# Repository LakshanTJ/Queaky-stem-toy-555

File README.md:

# 🎵 Queaky STEM Toy using 555 Timer 

A beginner-friendly **embedded systems project** that generates a squeaky sound using the **555 Timer IC in astable mode**.
This project demonstrates the complete workflow from **circuit design →  PCB design using KiCad**.

---

## 🧰 Components Used

* IC 555 Timer ×1
* 9V Battery ×1
* 9V Battery Connector ×1
* 5–12V Buzzer ×1
* 1kΩ Resistor ×1
* 10kΩ Resistor ×1
* 1nF Ceramic Capacitor ×1
* 100µF Electrolytic Capacitor ×1
* Breadboard / PCB

---

## ⚙️ How It Works

The circuit uses the **555 Timer in astable mode** to generate a continuous square wave signal.

* The resistor-capacitor network controls oscillation frequency
* Output is generated at **Pin 3** of the 555 timer
* The buzzer converts electrical pulses into sound
* The capacitor ensures stable operation

---

## 🔄 Working Principle

1. Capacitor charges through resistors
2. Voltage reaches threshold level
3. 555 timer switches state
4. Capacitor discharges
5. Cycle repeats continuously

This rapid switching produces an audible tone.

---

## 📊 Frequency Formula

The output frequency is determined by:

f ≈ 1.44 / ((R1 + 2R2) × C)

Where:

* R1 = 1kΩ
* R2 = 10kΩ
* C = 1nF
---

## 🛠️ PCB Design Workflow (KiCad)

This project was designed using **KiCad**, an industry-relevant open-source EDA tool.

### Steps followed:

1. Created schematic in KiCad
2. Assigned footprints to components
3. Switched to PCB editor
4. Placed components strategically
5. Routed tracks with proper connections
6. Performed Design Rule Check (DRC)
7. Generated Gerber files for manufacturing

---

## 🧠 Skills Demonstrated

* 555 Timer (Astable Mode)
* Analog electronics fundamentals
* Breadboard prototyping & debugging
* KiCad schematic design
* PCB layout and routing
* Design Rule Check (DRC) validation
* Hardware development workflow

---

## 🎯 Why This Project Matters

This project demonstrates practical skills required for **Embedded Systems / IoT internships**:

* Hands-on circuit design and testing
* Experience with PCB design tools (KiCad)
* Understanding of hardware-level behavior
* Ability to convert theory into real-world implementation

---

## 🚀 Future Improvements

* Add potentiometer for adjustable frequency
* Replace buzzer with speaker for tone variation
* Develop enclosure for real-world usage

---

## 📂 KiCad Files

All design files are available in the `kicad-files/` directory:

* Schematic file (.kicad_sch)
* PCB layout file (.kicad_pcb)

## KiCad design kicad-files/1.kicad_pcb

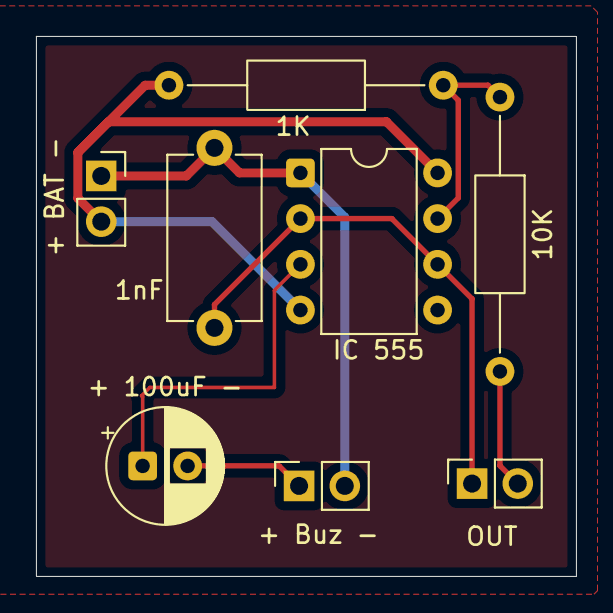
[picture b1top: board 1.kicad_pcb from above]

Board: 2 copper layers, 30.0 x 30.0 mm, 8 parts (0 on the bottom side), 7 nets.

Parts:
1K: 1K; R_Axial_DIN0207_L6.3mm_D2.5mm_P15.24mm_Horizontal
1nF: 1nF; C_Disc_D9.0mm_W5.0mm_P10.00mm
10K: 10K; R_Axial_DIN0207_L6.3mm_D2.5mm_P15.24mm_Horizontal
+ 100uF -: 100uF; CP_Radial_D6.3mm_P2.50mm
+ BAT -: Battery; PinSocket_1x02_P2.54mm_Vertical
+ Buz -: Buzzer; PinSocket_1x02_P2.54mm_Vertical
IC 555: NE555P; DIP-8_W7.62mm
OUT: Hoomans; PinSocket_1x02_P2.54mm_Vertical

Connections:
/DIS: 1K.1, 10K.1, IC 555.7 (DIS)
/Output: + 100uF -.1, IC 555.3 (Q)
/TR: 1nF.2, IC 555.2 (TR), IC 555.6 (THR), OUT.1
GND: 1nF.1, + BAT -.1, + Buz -.2, IC 555.1 (GND)
unnamed: + 100uF -.2, + Buz -.1
unnamed: 10K.2, OUT.2
VCC: 1K.2, + BAT -.2, IC 555.4 (R), IC 555.8 (VCC)

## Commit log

2026-04-29 reade me
2026-04-29 images
2026-04-29 Create images
2026-04-29 Create 1
2026-04-29 Create kicad-files
2026-04-29 Rename 1.kicad_pcb to queaky-toy.kicad_pcb
2026-04-29 Rename 1.kicad_sch to queaky-toy.kicad_sch
